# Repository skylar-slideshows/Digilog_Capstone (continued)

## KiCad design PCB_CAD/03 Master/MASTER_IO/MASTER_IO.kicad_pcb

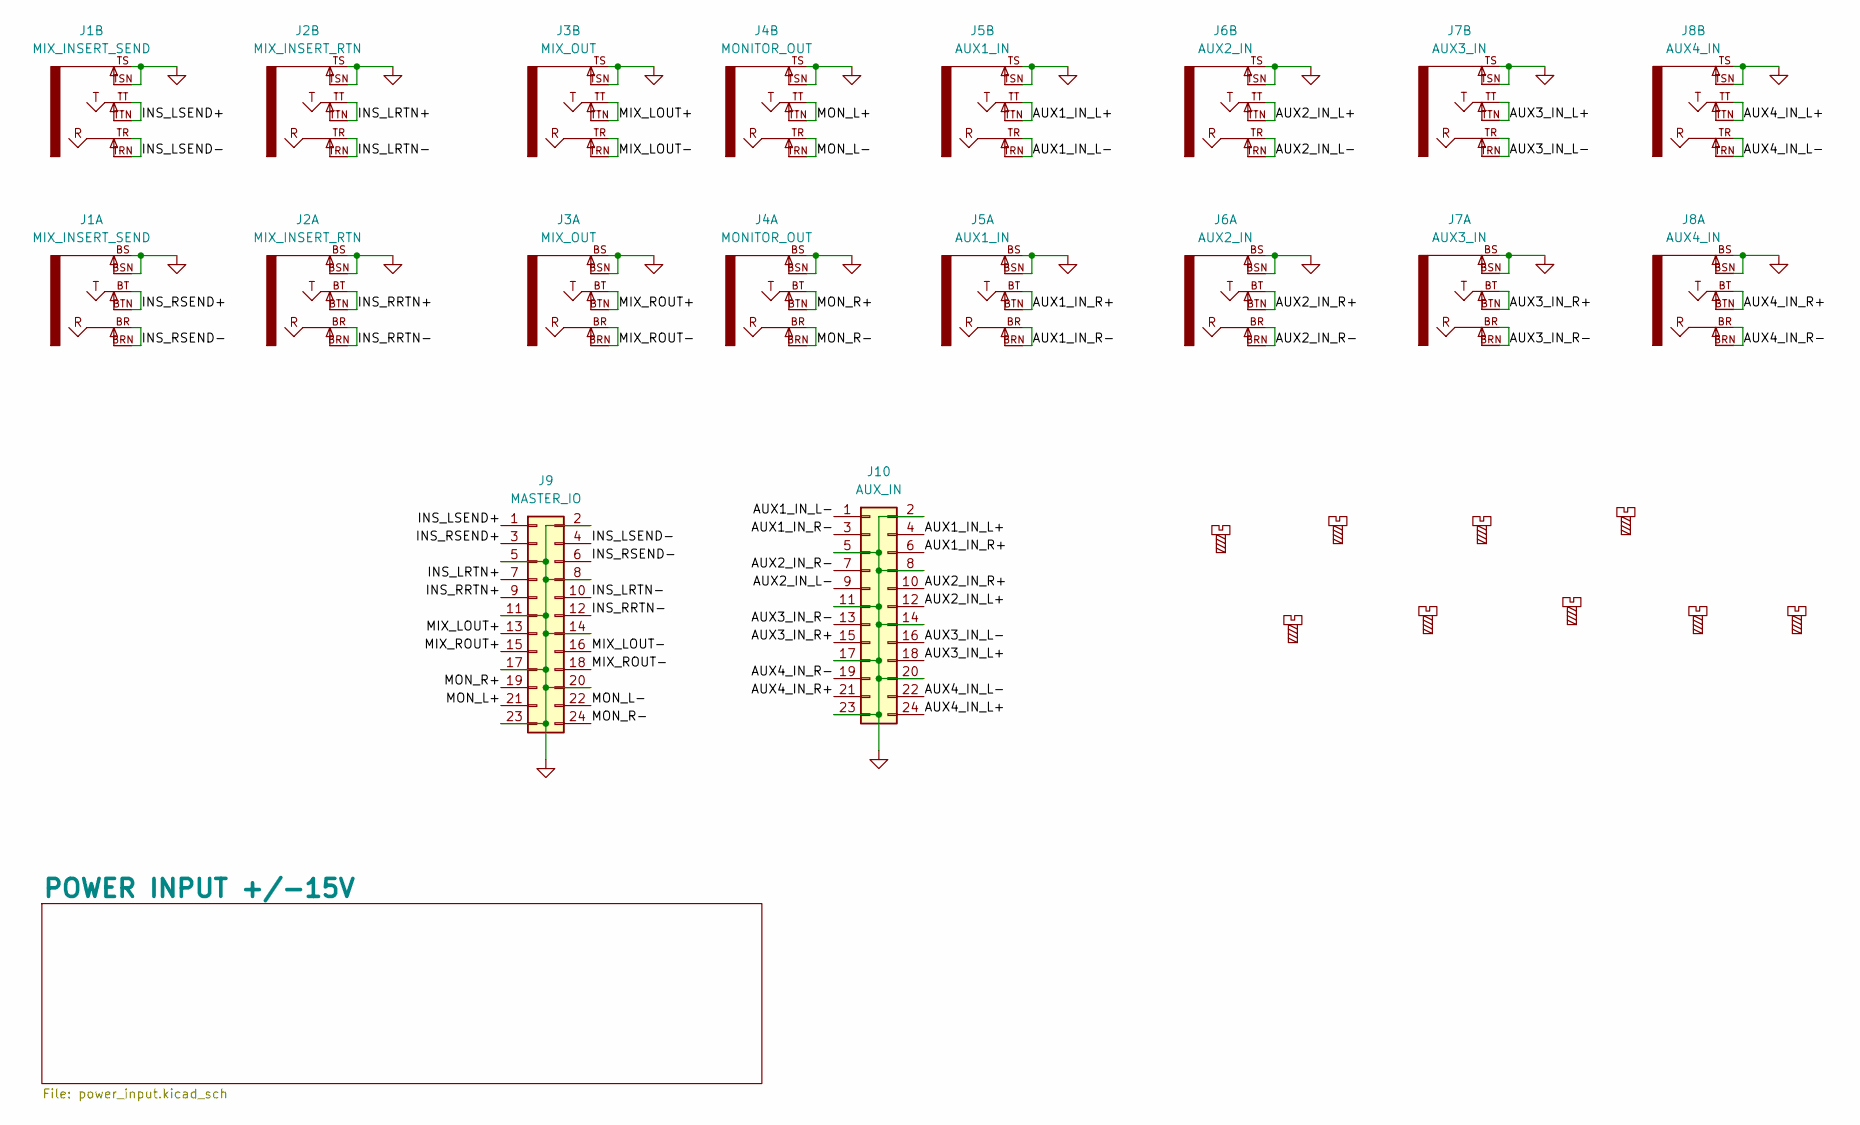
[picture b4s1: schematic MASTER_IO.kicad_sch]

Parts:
H1, H2, H3, H4, H5, H6, H7, H8, H9: MountingScrew; MountingHole_3.2mm_M3
J1: MIX_INSERT_SEND; ACJS-MHDC; MPN ACJS-MHDC
J2: MIX_INSERT_RTN; ACJS-MHDC; MPN ACJS-MHDC
J3: MIX_OUT; ACJS-MHDC; MPN ACJS-MHDC
J4: MONITOR_OUT; ACJS-MHDC; MPN ACJS-MHDC
J5: AUX1_IN; ACJS-MHDC; MPN ACJS-MHDC
J6: AUX2_IN; ACJS-MHDC; MPN ACJS-MHDC
J7: AUX3_IN; ACJS-MHDC; MPN ACJS-MHDC
J8: AUX4_IN; ACJS-MHDC; MPN ACJS-MHDC
J9: MASTER_IO; IDC-Header_2x12_P2.54mm_Vertical
J10: AUX_IN; IDC-Header_2x12_P2.54mm_Vertical

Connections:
/AUX1_IN_L+: J5.TT, J5.TTN, J10.4
/AUX1_IN_L-: J5.TR, J5.TRN, J10.1
/AUX1_IN_R+: J5.BT, J5.BTN, J10.6
/AUX1_IN_R-: J5.BR, J5.BRN, J10.3
/AUX2_IN_L+: J6.TT, J6.TTN, J10.12
/AUX2_IN_L-: J6.TR, J6.TRN, J10.9
/AUX2_IN_R+: J6.BT, J6.BTN, J10.10
/AUX2_IN_R-: J6.BR, J6.BRN, J10.7
/AUX3_IN_L+: J7.TT, J7.TTN, J10.18
/AUX3_IN_L-: J7.TR, J7.TRN, J10.16
/AUX3_IN_R+: J7.BT, J7.BTN, J10.15
/AUX3_IN_R-: J7.BR, J7.BRN, J10.13
/AUX4_IN_L+: J8.TT, J8.TTN, J10.24
/AUX4_IN_L-: J8.TR, J8.TRN, J10.22
/AUX4_IN_R+: J8.BT, J8.BTN, J10.21
/AUX4_IN_R-: J8.BR, J8.BRN, J10.19
/INS_LRTN+: J2.TT, J2.TTN, J9.7
/INS_LRTN-: J2.TR, J2.TRN, J9.10
/INS_LSEND+: J1.TT, J1.TTN, J9.1
/INS_LSEND-: J1.TR, J1.TRN, J9.4
/INS_RRTN+: J2.BT, J2.BTN, J9.9
/INS_RRTN-: J2.BR, J2.BRN, J9.12
/INS_RSEND+: J1.BT, J1.BTN, J9.3
/INS_RSEND-: J1.BR, J1.BRN, J9.6
/MIX_LOUT+: J3.TT, J3.TTN, J9.13
/MIX_LOUT-: J3.TR, J3.TRN, J9.16
/MIX_ROUT+: J3.BT, J3.BTN, J9.15
/MIX_ROUT-: J3.BR, J3.BRN, J9.18
/MON_L+: J4.TT, J4.TTN, J9.21
/MON_L-: J4.TR, J4.TRN, J9.22
/MON_R+: J4.BT, J4.BTN, J9.19
/MON_R-: J4.BR, J4.BRN, J9.24
GND: J1.BS, J1.BSN, J1.TS, J1.TSN, J2.BS, J2.BSN, J2.TS, J2.TSN, J3.BS, J3.BSN, J3.TS, J3.TSN, J4.BS, J4.BSN, J4.TS, J4.TSN, J5.BS, J5.BSN, J5.TS, J5.TSN, J6.BS, J6.BSN, J6.TS, J6.TSN, J7.BS, J7.BSN, J7.TS, J7.TSN, J8.BS, J8.BSN, J8.TS, J8.TSN, J9.2, J9.5, J9.8, J9.11, J9.14, J9.17, J9.20, J9.23, J10.2, J10.5, J10.8, J10.11, J10.14, J10.17, J10.20, J10.23; also elsewhere on the board

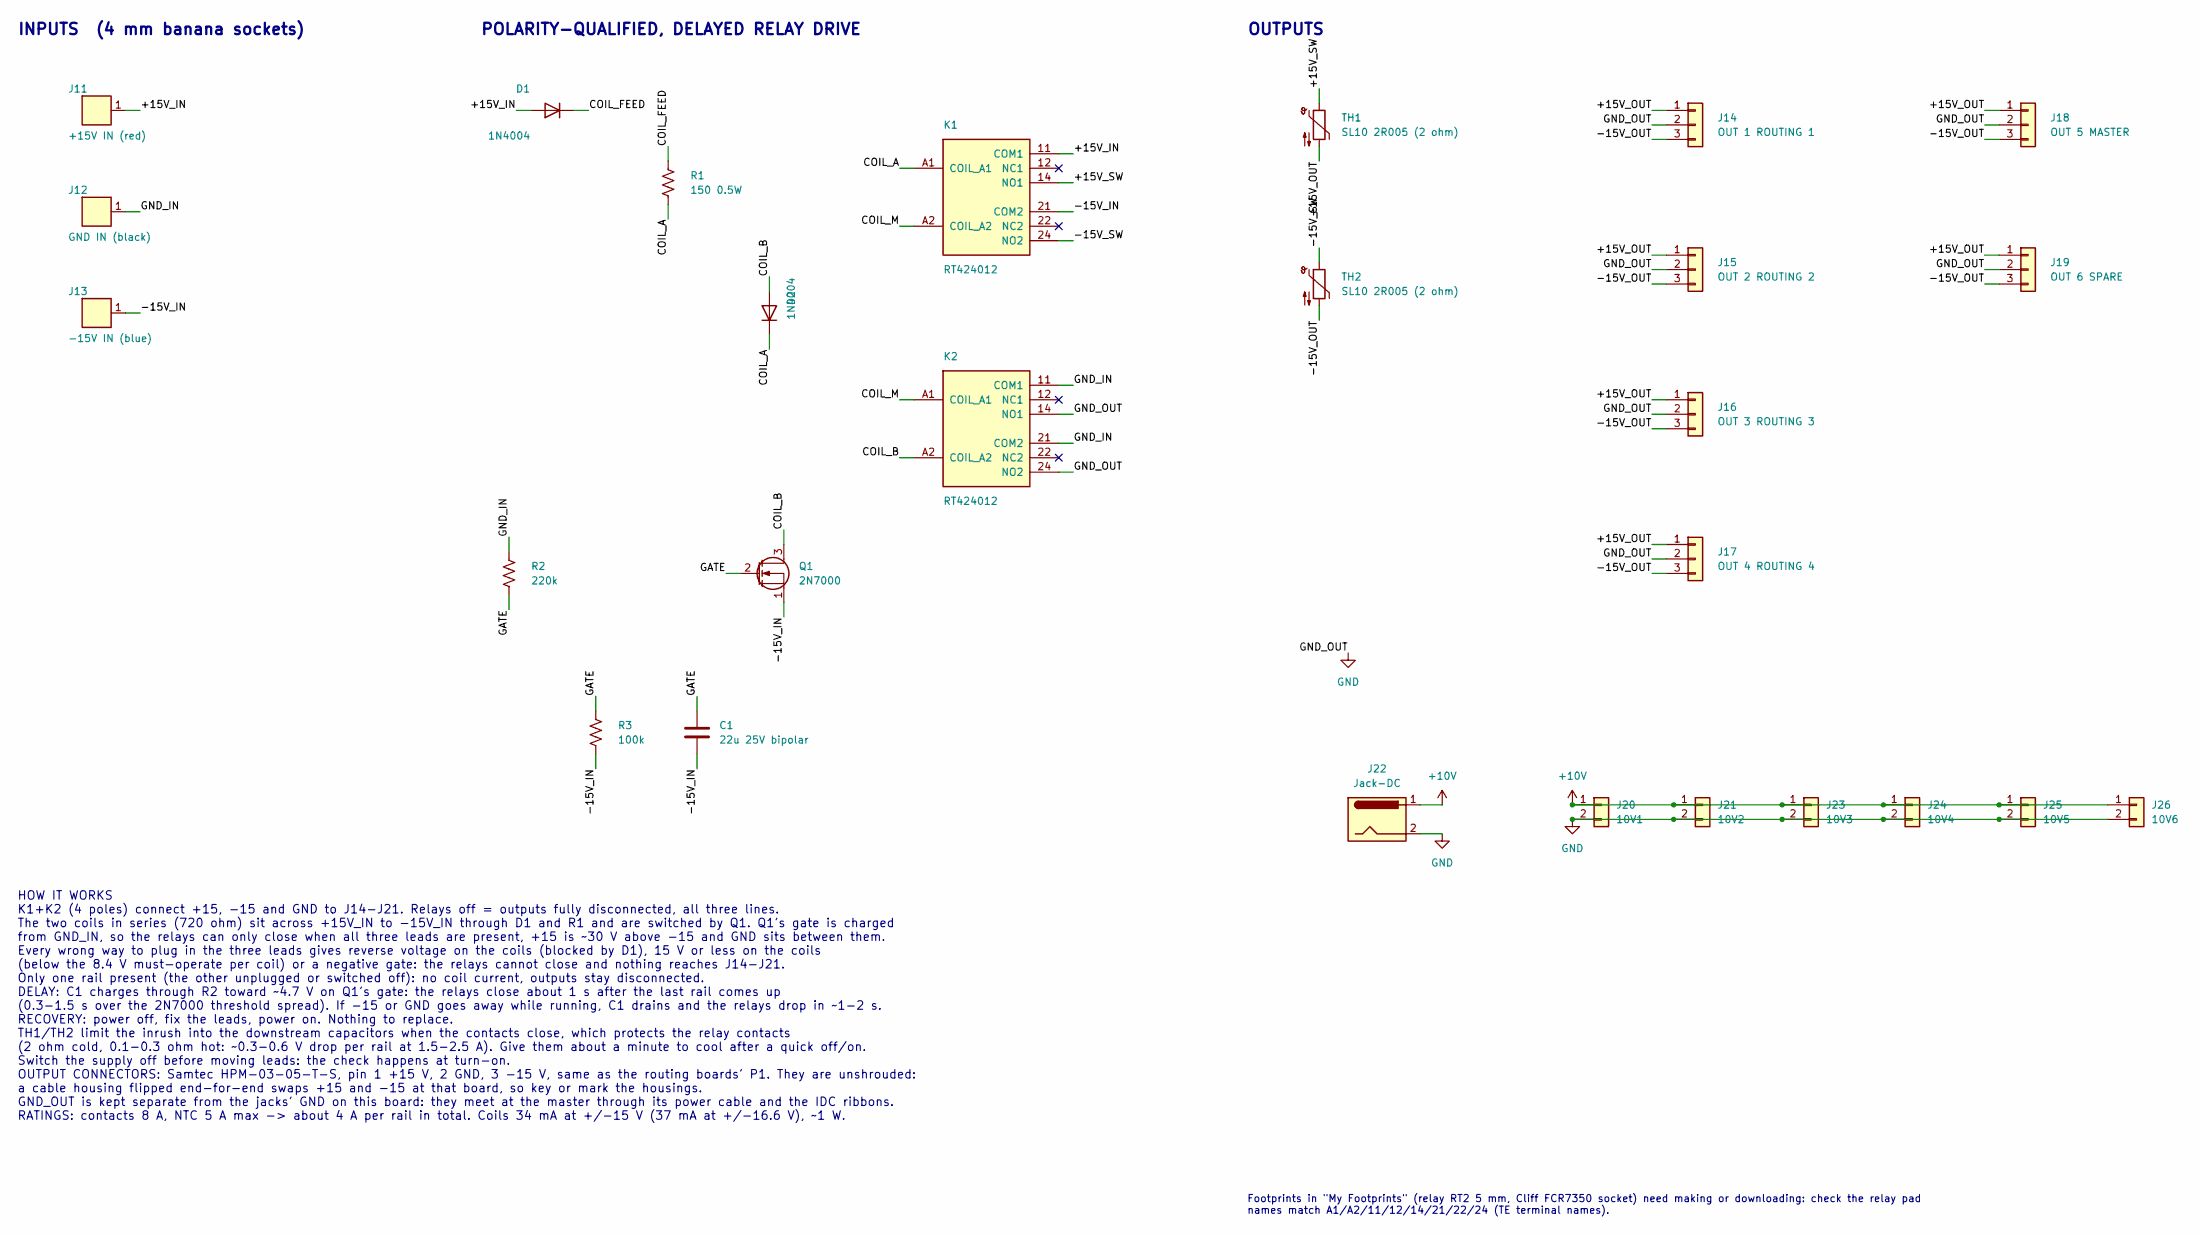
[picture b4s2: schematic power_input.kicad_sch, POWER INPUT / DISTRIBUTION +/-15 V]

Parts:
C1: 22u 25V bipolar; C_Radial_D6.3mm_H11.0mm_P2.50mm; MPN ECA-1EEN220
D1, D2: 1N4004; D_DO-41_SOD81_P10.16mm_Horizontal; MPN 1N4004G
J11: +15V IN (red); FCR7350; MPN FCR7350R
J12: GND IN (black); FCR7350; MPN FCR7350B
J13: -15V IN (blue); FCR7350; MPN FCR7350L
J14: OUT 1 ROUTING 1; Samtec_HPM-03-05-x-S_Straight_1x03_Pitch5.08mm; MPN HPM-03-05-T-S
J15: OUT 2 ROUTING 2; Samtec_HPM-03-05-x-S_Straight_1x03_Pitch5.08mm; MPN HPM-03-05-T-S
J16: OUT 3 ROUTING 3; Samtec_HPM-03-05-x-S_Straight_1x03_Pitch5.08mm; MPN HPM-03-05-T-S
J17: OUT 4 ROUTING 4; Samtec_HPM-03-05-x-S_Straight_1x03_Pitch5.08mm; MPN HPM-03-05-T-S
J18: OUT 5 MASTER; Samtec_HPM-03-05-x-S_Straight_1x03_Pitch5.08mm; MPN HPM-03-05-T-S
J19: OUT 6 SPARE; Samtec_HPM-03-05-x-S_Straight_1x03_Pitch5.08mm; MPN HPM-03-05-T-S
J20: 10V1; PinHeader_1x02_P2.54mm_Vertical
J21: 10V2; PinHeader_1x02_P2.54mm_Vertical
J22: Jack-DC; BarrelJack_Horizontal
J23: 10V3; PinHeader_1x02_P2.54mm_Vertical
J24: 10V4; PinHeader_1x02_P2.54mm_Vertical
J25: 10V5; PinHeader_1x02_P2.54mm_Vertical
J26: 10V6; PinHeader_1x02_P2.54mm_Vertical
K1, K2: RT424012; Relay_DPDT_Schrack-RT2-FormC_RM5mm; MPN RT424012
Q1: 2N7000; TO-92_Inline_Wide; MPN 2N7000
R1: 150 0.5W; R_Axial_DIN0309_L9.0mm_D3.2mm_P12.70mm_Horizontal; MPN MFR50SFTE52-150R
R2: 220k; R_Axial_DIN0207_L6.3mm_D2.5mm_P10.16mm_Horizontal; MPN MFR-25FBF52-220K
R3: 100k; R_Axial_DIN0207_L6.3mm_D2.5mm_P10.16mm_Horizontal; MPN MFR-25FBF52-100K
TH1, TH2: SL10 2R005 (2 ohm); C_Disc_D10.0mm_W2.5mm_P5.00mm; MPN SL10 2R005

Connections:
+10V: J20.1, J21.1, J22.1, J23.1, J24.1, J25.1, J26.1
/POWER INPUT +/-15V/+15V_IN: D1.2 (A), J11.1 (~_1), K1.11 (COM1)
/POWER INPUT +/-15V/+15V_OUT: J14.1, J15.1, J16.1, J17.1, J18.1, J19.1, TH1.2
/POWER INPUT +/-15V/+15V_SW: K1.14 (NO1), TH1.1
/POWER INPUT +/-15V/-15V_IN: C1.2, J13.1 (~_1), K1.21 (COM2), Q1.1 (S), R3.2
/POWER INPUT +/-15V/-15V_OUT: J14.3, J15.3, J16.3, J17.3, J18.3, J19.3, TH2.2
/POWER INPUT +/-15V/-15V_SW: K1.24 (NO2), TH2.1
/POWER INPUT +/-15V/COIL_A: D2.1 (K), K1.A1 (COIL_A1), R1.2
/POWER INPUT +/-15V/COIL_B: D2.2 (A), K2.A2 (COIL_A2), Q1.3 (D)
/POWER INPUT +/-15V/COIL_FEED: D1.1 (K), R1.1
/POWER INPUT +/-15V/COIL_M: K1.A2 (COIL_A2), K2.A1 (COIL_A1)
/POWER INPUT +/-15V/GATE: C1.1, Q1.2 (G), R2.2, R3.1
/POWER INPUT +/-15V/GND_IN: J12.1 (~_1), K2.11 (COM1), K2.21 (COM2), R2.1
GND: J14.2, J15.2, J16.2, J17.2, J18.2, J19.2, J20.2, J21.2, J22.2, J23.2, J24.2, J25.2, J26.2, K2.14 (NO1), K2.24 (NO2); also elsewhere on the board

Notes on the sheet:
INPUTS (4 mm banana sockets)
HOW IT WORKS K1+K2 (4 poles) connect +15, -15 and GND to J14-J21. Relays off = outputs fully disconnected, all three lines. The two coils in series (720 ohm) sit across +15V_IN to -15V_IN through D1 and R1 and are switched by Q1. Q1's gate is charged from GND_IN, so the relays can only close when a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
POLARITY-QUALIFIED, DELAYED RELAY DRIVE
OUTPUTS
Footprints in "My Footprints" (relay RT2 5 mm, Cliff FCR7350 socket) need making or downloading: check the relay pad names match A1/A2/11/12/14/21/22/24 (TE terminal names).

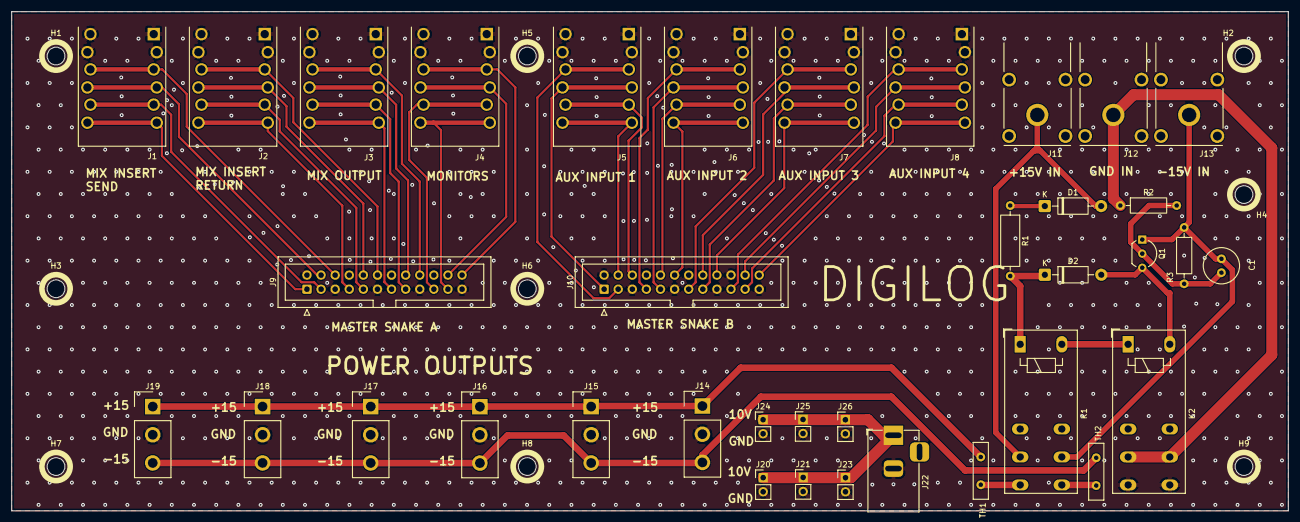
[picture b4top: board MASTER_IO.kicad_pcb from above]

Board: 2 copper layers, 230.0 x 89.9 mm, 46 parts (0 on the bottom side), 46 nets.

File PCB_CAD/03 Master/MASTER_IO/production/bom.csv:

Designator,Footprint,Quantity,Value,LCSC Part #
C1,C_Radial_D6.3mm_H11.0mm_P2.50mm,1,22u 25V bipolar,ECA-1EEN220
"D1, D2",D_DO-41_SOD81_P10.16mm_Horizontal,2,1N4004,1N4004G
J1,ACJS-MHDC,1,MIX_INSERT_SEND,ACJS-MHDC
J10,IDC-Header_2x12_P2.54mm_Vertical,1,AUX_IN,
J11,FCR7350,1,+15V IN (red),FCR7350R
J12,FCR7350,1,GND IN (black),FCR7350B
J13,FCR7350,1,-15V IN (blue),FCR7350L
J14,Samtec_HPM-03-05-x-S_Straight_1x03_Pitch5.08mm,1,OUT 1 ROUTING 1,HPM-03-05-T-S
J15,Samtec_HPM-03-05-x-S_Straight_1x03_Pitch5.08mm,1,OUT 2 ROUTING 2,HPM-03-05-T-S
J16,Samtec_HPM-03-05-x-S_Straight_1x03_Pitch5.08mm,1,OUT 3 ROUTING 3,HPM-03-05-T-S
J17,Samtec_HPM-03-05-x-S_Straight_1x03_Pitch5.08mm,1,OUT 4 ROUTING 4,HPM-03-05-T-S
J18,Samtec_HPM-03-05-x-S_Straight_1x03_Pitch5.08mm,1,OUT 5 MASTER,HPM-03-05-T-S
J19,Samtec_HPM-03-05-x-S_Straight_1x03_Pitch5.08mm,1,OUT 6 SPARE,HPM-03-05-T-S
J2,ACJS-MHDC,1,MIX_INSERT_RTN,ACJS-MHDC
J20,PinHeader_1x02_P2.54mm_Vertical,1,10V1,
J21,PinHeader_1x02_P2.54mm_Vertical,1,10V2,
J22,BarrelJack_Horizontal,1,Jack-DC,
J23,PinHeader_1x02_P2.54mm_Vertical,1,10V3,
J24,PinHeader_1x02_P2.54mm_Vertical,1,10V4,
J25,PinHeader_1x02_P2.54mm_Vertical,1,10V5,
J26,PinHeader_1x02_P2.54mm_Vertical,1,10V6,
J3,ACJS-MHDC,1,MIX_OUT,ACJS-MHDC
J4,ACJS-MHDC,1,MONITOR_OUT,ACJS-MHDC
J5,ACJS-MHDC,1,AUX1_IN,ACJS-MHDC
J6,ACJS-MHDC,1,AUX2_IN,ACJS-MHDC
J7,ACJS-MHDC,1,AUX3_IN,ACJS-MHDC
J8,ACJS-MHDC,1,AUX4_IN,ACJS-MHDC
J9,IDC-Header_2x12_P2.54mm_Vertical,1,MASTER_IO,
"K1, K2",Relay_DPDT_Schrack-RT2-FormC_RM5mm,2,RT424012,RT424012
Q1,TO-92_Inline_Wide,1,2N7000,2N7000
R1,R_Axial_DIN0309_L9.0mm_D3.2mm_P12.70mm_Horizontal,1,150 0.5W,MFR50SFTE52-150R
R2,R_Axial_DIN0207_L6.3mm_D2.5mm_P10.16mm_Horizontal,1,220k,MFR-25FBF52-220K
R3,R_Axial_DIN0207_L6.3mm_D2.5mm_P10.16mm_Horizontal,1,100k,MFR-25FBF52-100K
"TH1, TH2",C_Disc_D10.0mm_W2.5mm_P5.00mm,2,SL10 2R005 (2 ohm),SL10 2R005

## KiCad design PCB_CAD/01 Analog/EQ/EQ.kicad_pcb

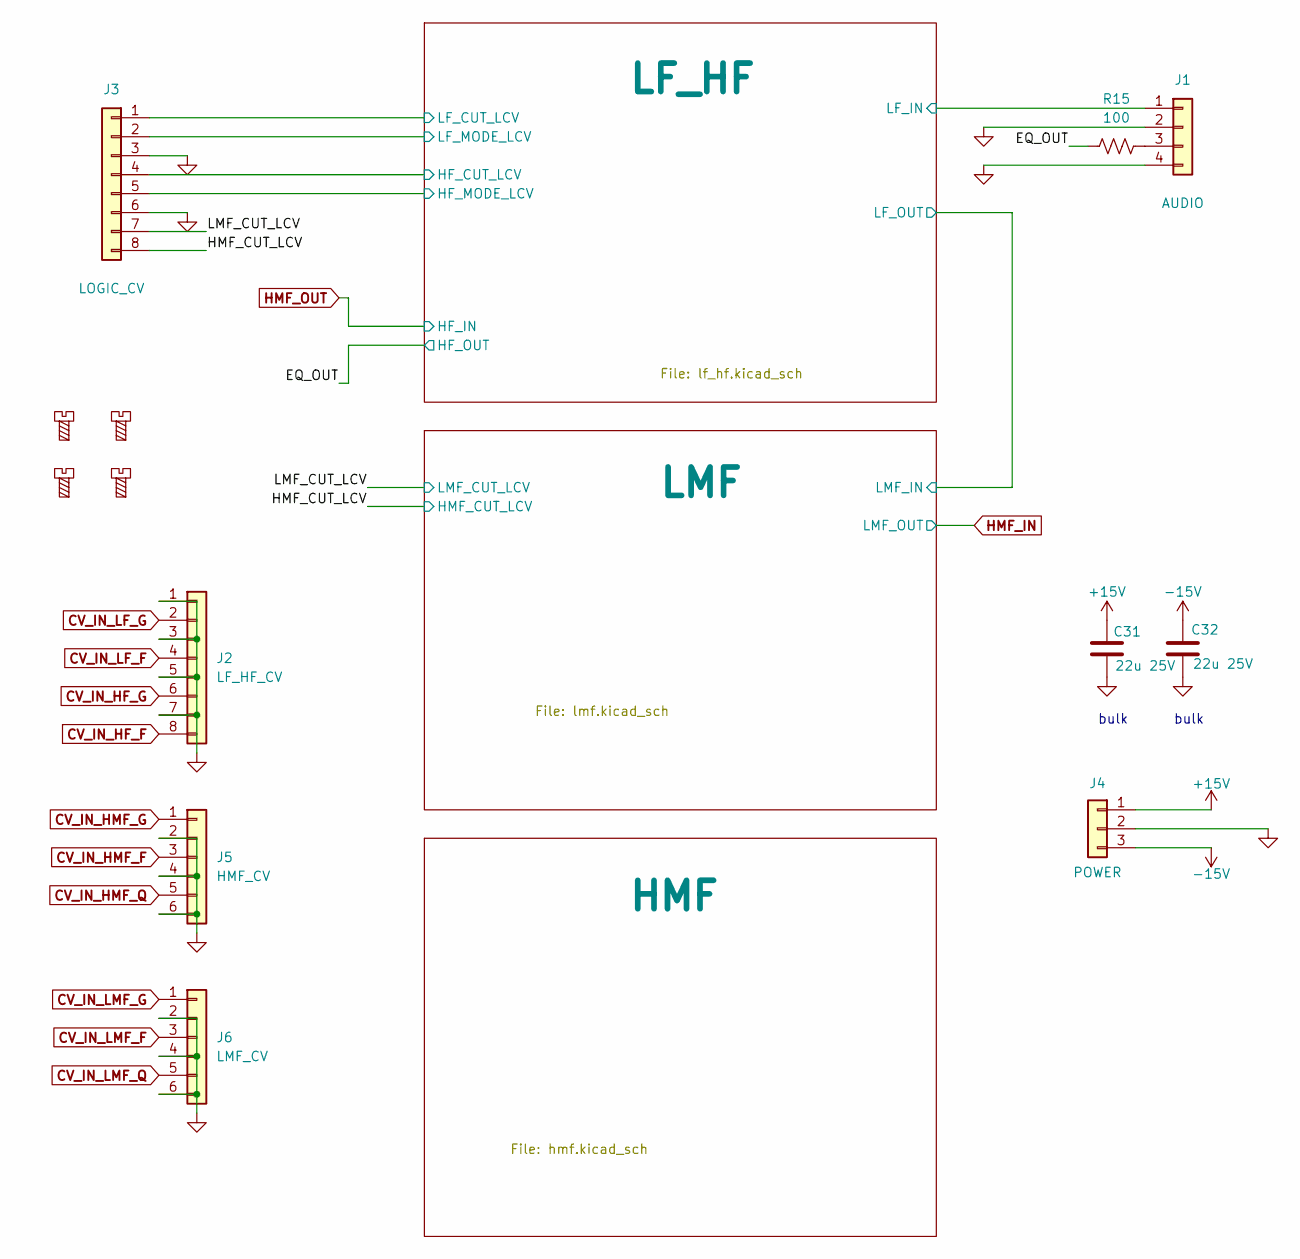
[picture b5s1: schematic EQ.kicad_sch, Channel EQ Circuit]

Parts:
C31, C32: 22u 25V; C_1210_3225Metric; LCSC C21397
H1, H2, H3, H4: MountingScrew; MountingHole_2.2mm_M2; LCSC dnp
J1: AUDIO; PinHeader_1x04_P2.54mm_Vertical; LCSC dnp
J2: LF_HF_CV; PinHeader_1x08_P2.54mm_Vertical; LCSC dnp
J3: LOGIC_CV; PinHeader_1x08_P2.54mm_Vertical; LCSC dnp
J4: POWER; PinHeader_1x03_P2.54mm_Vertical; LCSC dnp
J5: HMF_CV; PinHeader_1x06_P2.54mm_Vertical; LCSC dnp
J6: LMF_CV; PinHeader_1x06_P2.54mm_Vertical; LCSC dnp
R15: 100; R_0402_1005Metric; LCSC C317909

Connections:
+15V: C31.1, J4.1; also elsewhere on the board
-15V: C32.1, J4.3; also elsewhere on the board
/EQ_OUT: R15.1; also elsewhere on the board
/HMF_CUT_LCV: J3.8; also elsewhere on the board
/LF_HF/HF_CUT_LCV: J3.4; also elsewhere on the board
/LF_HF/HF_MODE_LCV: J3.5; also elsewhere on the board
/LF_HF/LF_CUT_LCV: J3.1; also elsewhere on the board
/LF_HF/LF_IN: J1.1; also elsewhere on the board
/LF_HF/LF_MODE_LCV: J3.2; also elsewhere on the board
/LMF_CUT_LCV: J3.7; also elsewhere on the board
CV_IN_HF_F: J2.8; also elsewhere on the board
CV_IN_HF_G: J2.6; also elsewhere on the board
CV_IN_HMF_F: J5.3; also elsewhere on the board
CV_IN_HMF_G: J5.1; also elsewhere on the board
CV_IN_HMF_Q: J5.5; also elsewhere on the board
CV_IN_LF_F: J2.4; also elsewhere on the board
CV_IN_LF_G: J2.2; also elsewhere on the board
CV_IN_LMF_F: J6.3; also elsewhere on the board
CV_IN_LMF_G: J6.1; also elsewhere on the board
CV_IN_LMF_Q: J6.5; also elsewhere on the board
GND: C31.2, C32.2, J1.2, J1.4, J2.1, J2.3, J2.5, J2.7, J3.3, J3.6, J4.2, J5.2, J5.4, J5.6, J6.2, J6.4, J6.6; also elsewhere on the board
unnamed: J1.3, R15.2

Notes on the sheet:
bulk

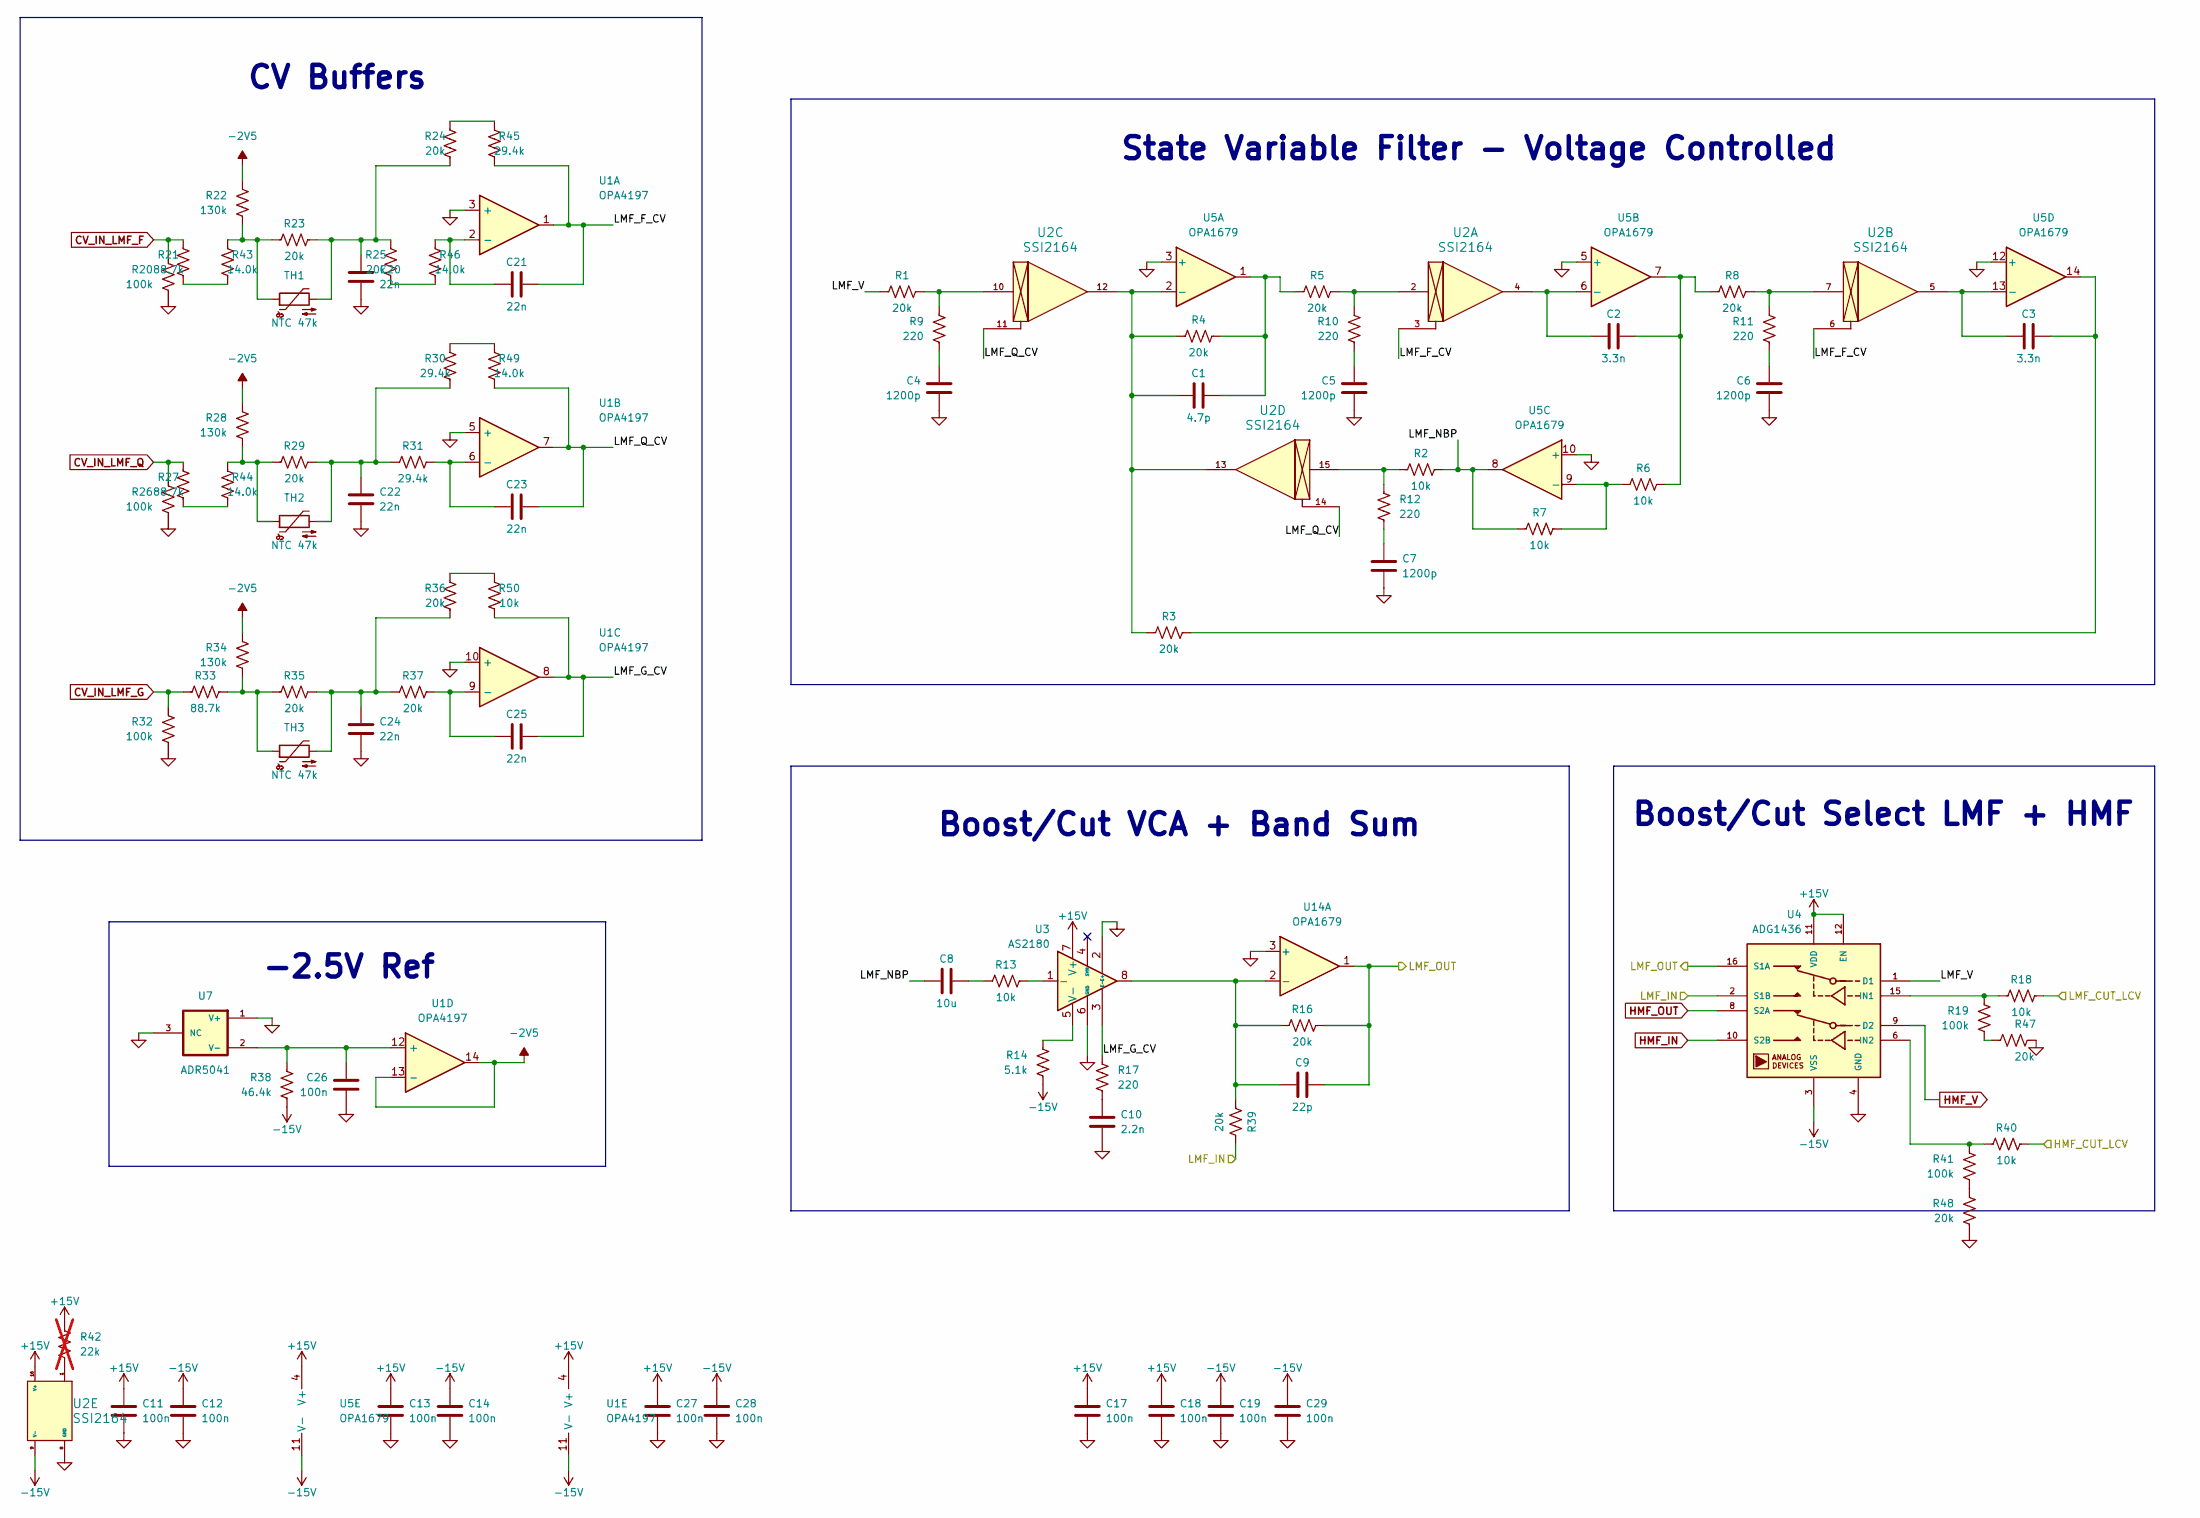
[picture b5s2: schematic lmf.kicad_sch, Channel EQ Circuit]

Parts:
C1: 4.7p; C_0603_1608Metric; LCSC C282071
C2, C3: 3.3n; C_0603_1608Metric; LCSC C107048
C4, C5, C6, C7: 1200p; C_1206_3216Metric; LCSC C527278
C8: 10u; CP_Elec_6.3x5.4_Nichicon; LCSC C340735
C9: 22p; C_0603_1608Metric; LCSC C105620
C10: 2.2n; C_0805_2012Metric; LCSC C107103
C11, C12, C13, C14, C17, C18, C19, C27, C28, C29: 100n; C_0603_1608Metric; LCSC C1591
C20, C21, C22, C23, C24, C25: 22n; C_1206_3216Metric; LCSC C7500389
C26: 100n; C_0603_1608Metric; LCSC C1590
R1, R3, R4, R5, R8, R16, R23, R24, R25, R29, R35, R36, R37, R39, R47, R48: 20k; R_0603_1608Metric; LCSC C311888
R2, R6, R7, R13, R18, R40, R50: 10k; R_0603_1608Metric; LCSC C95204
R9, R10, R11, R12, R17: 220; R_0603_1608Metric; LCSC C318124
R14: 5.1k; R_0603_1608Metric; LCSC C122969
R19, R20, R26, R32, R41: 100k; R_0603_1608Metric; LCSC C122538
R21, R27, R33: 88.7k; R_0603_1608Metric; LCSC C728599
R22, R28, R34: 130k; R_0603_1608Metric; LCSC C473257
R30, R31, R45: 29.4k; R_0603_1608Metric; LCSC C667085
R38: 46.4k; R_0603_1608Metric; LCSC C861420
R42: 22k; R_0603_1608Metric; LCSC C335085; not fitted
R43, R44, R46, R49: 14.0k; R_0603_1608Metric; LCSC C705941
TH1, TH2, TH3: NTC 47k; R_Axial_DIN0207_L6.3mm_D2.5mm_P2.54mm_Vertical; MPN NTCLE100E3473JB0; LCSC dnp
U1: OPA4197; SOIC-14_3.9x8.7mm_P1.27mm; LCSC C2058532
U2: SSI2164; SSI2164_breakout; LCSC dnp
U3: AS2180; PinHeader_1x08_P2.54mm_Vertical; LCSC dnp
U4: ADG1436; Analog_LFCSP-16-1EP_4x4mm_P0.65mm_EP2.1x2.1mm; LCSC C655227
U5, U14: OPA1679; SOIC-14_3.9x8.7mm_P1.27mm; LCSC C2878631
U7: ADR5041; SOT-23; MPN ADR5041ARTZ-R2; LCSC C659596

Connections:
+15V: C11.1, C13.1, C17.1, C18.1, C27.1, R42.1, U1.4 (V+), U2.16 (V+), U3.7 (V+), U4.11 (VDD), U4.12 (EN), U5.4 (V+); also elsewhere on the board
-2V5: R22.1, R28.1, R34.1, U1.13 (-), U1.14; also elsewhere on the board
-15V: C12.1, C14.1, C19.1, C28.1, C29.1, R14.2, R38.2, U1.11 (V-), U2.9 (V-), U4.3 (VSS), U5.11 (V-); also elsewhere on the board
/HMF_CUT_LCV: R40.2; also elsewhere on the board
/LF_HF/LF_OUT: R39.2, U4.2 (S1B); also elsewhere on the board
/LMF/LMF_F_CV: C21.2, R45.2, U1.1, U2.3, U2.6
/LMF/LMF_G_CV: C25.2, R17.1, R50.2, U1.8, U3.3 (E-)
/LMF/LMF_NBP: C8.1, R2.2, R7.1, U5.8
/LMF/LMF_Q_CV: C23.2, R49.2, U1.7, U2.11, U2.14
/LMF/LMF_V: R1.1, U4.1 (D1)
/LMF_CUT_LCV: R18.2; also elsewhere on the board
CV_IN_LMF_F: R20.1, R21.1; also elsewhere on the board
CV_IN_LMF_G: R32.1, R33.1; also elsewhere on the board
CV_IN_LMF_Q: R26.1, R27.1; also elsewhere on the board
GND: C4.2, C5.2, C6.2, C7.2, C10.2, C11.2, C12.2, C13.2, C14.2, C17.2, C18.2, C19.2, C20.2, C22.2, C24.2, C26.2, C27.2, C28.2, C29.2, R20.2, R26.2, R32.2, R47.2, R48.2, U1.3 (+), U1.5 (+), U1.10 (+), U2.8 (GND), U3.2 (E+), U3.6 (GND), U4.4 (GND), U5.3 (+), U5.5 (+), U5.10 (+), U5.12 (+), U7.1 (V+), U7.3 (NC), U14.3 (+); also elsewhere on the board
HMF_IN: C9.2, R16.2, U4.10 (S2B), U4.16 (S1A), U14.1; also elsewhere on the board
HMF_OUT: U4.8 (S2A); also elsewhere on the board
HMF_V: U4.9 (D2); also elsewhere on the board
unnamed: C1.2, R4.2, R5.1, U5.1
unnamed: C2.2, R6.2, R8.1, U5.7
unnamed: C3.2, R3.2, U5.14
unnamed: C4.1, R9.2
unnamed: C5.1, R10.2
unnamed: C6.1, R11.2
unnamed: C7.1, R12.2
unnamed: C8.2, R13.1
unnamed: C10.1, R17.2
unnamed: C20.1, R23.2, R24.1, R25.1, TH1.2
unnamed: C22.1, R29.2, R30.1, R31.1, TH2.2
unnamed: C24.1, R35.2, R36.1, R37.1, TH3.2
unnamed: R1.2, R9.1, U2.10
unnamed: R5.2, R10.1, U2.2
unnamed: R8.2, R11.1, U2.7
unnamed: R2.1, R12.1, U2.15
unnamed: R19.2, R47.1
unnamed: R21.2, R43.1
unnamed: R22.2, R23.1, R43.2, TH1.1
unnamed: R24.2, R45.1
unnamed: R25.2, R46.1
unnamed: R27.2, R44.1
unnamed: R28.2, R29.1, R44.2, TH2.1
unnamed: R30.2, R49.1
unnamed: R33.2, R34.2, R35.1, TH3.1
unnamed: R36.2, R50.1
unnamed: R41.2, R48.1
unnamed: R42.2, U2.1
unnamed: C21.1, R46.2, U1.2 (-)
unnamed: C23.1, R31.2, U1.6 (-)
unnamed: C25.1, R37.2, U1.9 (-)
unnamed: C26.1, R38.1, U1.12 (+), U7.2 (V-)
unnamed: R13.2, U3.1 (-)
unnamed: R14.1, U3.5 (V-)
unnamed: R18.1, R19.1, U4.15 (IN1)
unnamed: R40.1, R41.1, U4.6 (IN2)
unnamed: C1.1, R3.1, R4.1, U2.12, U2.13, U5.2 (-)
unnamed: C2.1, U2.4, U5.6 (-)
unnamed: R6.1, R7.2, U5.9 (-)
unnamed: C3.1, U2.5, U5.13 (-)
unnamed: C9.1, R16.1, R39.1, U3.8, U14.2 (-)

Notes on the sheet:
Boost/Cut Select LMF + HMF
Boost/Cut VCA + Band Sum
-2.5V Ref
State Variable Filter - Voltage Controlled
CV Buffers
